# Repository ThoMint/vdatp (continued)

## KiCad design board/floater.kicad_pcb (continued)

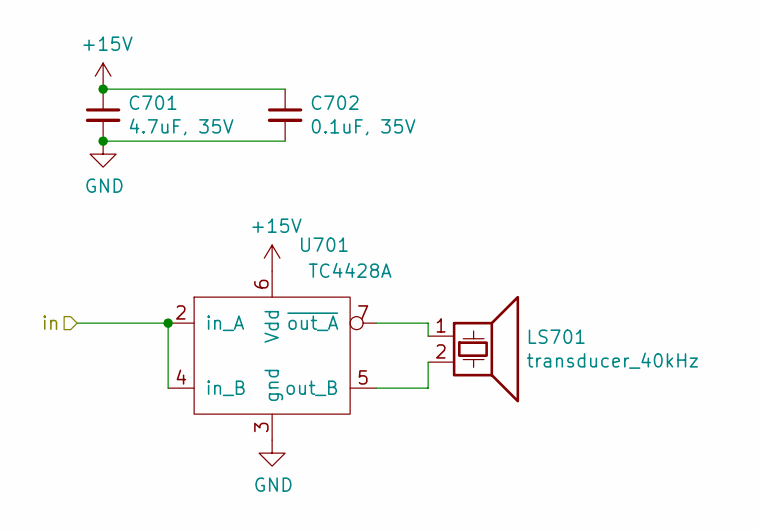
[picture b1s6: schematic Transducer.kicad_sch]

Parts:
C701: 4.7uF, 35V; C_1206_3216Metric
C702: 0.1uF, 35V; C_0805_2012Metric
LS701: transducer_40kHz; MSO-P1040H07T
U701: TC4428A; SO-8_3.9x4.9mm_P1.27mm

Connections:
+15V: C701.1, C702.1, U701.6 (Vdd); also elsewhere on the board
/FPGA2/t41: U701.2 (in_A), U701.4 (in_B); also elsewhere on the board
GND: C701.2, C702.2, U701.3 (gnd); also elsewhere on the board
unnamed: LS701.1, U701.7 (~out_A)
unnamed: LS701.2, U701.5 (out_B)

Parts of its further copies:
C601, C801, C901, C1001, C1101, C1201, C1301, C1401, C1501, C1601, C1701, C1801, C1901, C2001, C2101, C2201, C2301, C2401, C2501, C2601, C2701, C2801, C2901, C3001, C3101, C3201, C3301, C3401, C3501, C3601, C3701, C3801, C3901, C4001, C4101, C4201, C4301, C4401, C4501, C4601, C4701, C4801, C4901, C5001, C5101, C5201, C5301, C5401, C5501, C5601, C5701, C5801, C5901, C6001, C6101, C6201, C6301, C6401, C6501, C6601, C6701, C6801, C6901, C7001, C7101, C7201, C7301, C7401, C7501, C7601, C7701, C7801, C7901, C8001, C8101, C8201, C8301, C8401, C8501, C8601, C8701, C8801, C8901, C9001, C9101, C9201, C9301, C9401, C9501, C9601, C9701, C9801, C9901, C10001, C10101, C10201, C10301, C10401, C10501: 4.7uF, 35V; C_1206_3216Metric
C602, C802, C902, C1002, C1102, C1202, C1302, C1402, C1502, C1602, C1702, C1802, C1902, C2002, C2102, C2202, C2302, C2402, C2502, C2602, C2702, C2802, C2902, C3002, C3102, C3202, C3302, C3402, C3502, C3602, C3702, C3802, C3902, C4002, C4102, C4202, C4302, C4402, C4502, C4602, C4702, C4802, C4902, C5002, C5102, C5202, C5302, C5402, C5502, C5602, C5702, C5802, C5902, C6002, C6102, C6202, C6302, C6402, C6502, C6602, C6702, C6802, C6902, C7002, C7102, C7202, C7302, C7402, C7502, C7602, C7702, C7802, C7902, C8002, C8102, C8202, C8302, C8402, C8502, C8602, C8702, C8802, C8902, C9002, C9102, C9202, C9302, C9402, C9502, C9602, C9702, C9802, C9902, C10002, C10102, C10202, C10302, C10402, C10502: 0.1uF, 35V; C_0805_2012Metric
LS601, LS801, LS901, LS1001, LS1101, LS1201, LS1301, LS1401, LS1501, LS1601, LS1701, LS1801, LS1901, LS2001, LS2101, LS2201, LS2301, LS2401, LS2501, LS2601, LS2701, LS2801, LS2901, LS3001, LS3101, LS3201, LS3301, LS3401, LS3501, LS3601, LS3701, LS3801, LS3901, LS4001, LS4101, LS4201, LS4301, LS4401, LS4501, LS4601, LS4701, LS4801, LS4901, LS5001, LS5101, LS5201, LS5301, LS5401, LS5501, LS5601, LS5701, LS5801, LS5901, LS6001, LS6101, LS6201, LS6301, LS6401, LS6501, LS6601, LS6701, LS6801, LS6901, LS7001, LS7101, LS7201, LS7301, LS7401, LS7501, LS7601, LS7701, LS7801, LS7901, LS8001, LS8101, LS8201, LS8301, LS8401, LS8501, LS8601, LS8701, LS8801, LS8901, LS9001, LS9101, LS9201, LS9301, LS9401, LS9501, LS9601, LS9701, LS9801, LS9901, LS10001, LS10101, LS10201, LS10301, LS10401, LS10501: transducer_40kHz; MSO-P1040H07T
U601, U801, U901, U1001, U1101, U1201, U1301, U1401, U1501, U1601, U1701, U1801, U1901, U2001, U2101, U2201, U2301, U2401, U2501, U2601, U2701, U2801, U2901, U3001, U3101, U3201, U3301, U3401, U3501, U3601, U3701, U3801, U3901, U4001, U4101, U4201, U4301, U4401, U4501, U4601, U4701, U4801, U4901, U5001, U5101, U5201, U5301, U5401, U5501, U5601, U5701, U5801, U5901, U6001, U6101, U6201, U6301, U6401, U6501, U6601, U6701, U6801, U6901, U7001, U7101, U7201, U7301, U7401, U7501, U7601, U7701, U7801, U7901, U8001, U8101, U8201, U8301, U8401, U8501, U8601, U8701, U8801, U8901, U9001, U9101, U9201, U9301, U9401, U9501, U9601, U9701, U9801, U9901, U10001, U10101, U10201, U10301, U10401, U10501: TC4428A; SO-8_3.9x4.9mm_P1.27mm

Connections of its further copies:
+15V: C601.1, C602.1, C801.1, C802.1, C901.1, C902.1, C1001.1, C1002.1, C1101.1, C1102.1, C1201.1, C1202.1, C1301.1, C1302.1, C1401.1, C1402.1, C1501.1, C1502.1, C1601.1, C1602.1, C1701.1, C1702.1, C1801.1, C1802.1, C1901.1, C1902.1, C2001.1, C2002.1, C2101.1, C2102.1, C2201.1, C2202.1, C2301.1, C2302.1, C2401.1, C2402.1, C2501.1, C2502.1, C2601.1, C2602.1, C2701.1, C2702.1, C2801.1, C2802.1, C2901.1, C2902.1, C3001.1, C3002.1, C3101.1, C3102.1, C3201.1, C3202.1, C3301.1, C3302.1, C3401.1, C3402.1, C3501.1, C3502.1, C3601.1, C3602.1, C3701.1, C3702.1, C3801.1, C3802.1, C3901.1, C3902.1, C4001.1, C4002.1, C4101.1, C4102.1, C4201.1, C4202.1, C4301.1, C4302.1, C4401.1, C4402.1, C4501.1, C4502.1, C4601.1, C4602.1, C4701.1, C4702.1, C4801.1, C4802.1, C4901.1, C4902.1, C5001.1, C5002.1, C5101.1, C5102.1, C5201.1, C5202.1, C5301.1, C5302.1, C5401.1, C5402.1, C5501.1, C5502.1, C5601.1, C5602.1, C5701.1, C5702.1, C5801.1, C5802.1, C5901.1, C5902.1, C6001.1, C6002.1, C6101.1, C6102.1, C6201.1, C6202.1, C6301.1, C6302.1, C6401.1, C6402.1, C6501.1, C6502.1, C6601.1, C6602.1, C6701.1, C6702.1, C6801.1, C6802.1, C6901.1, C6902.1, C7001.1, C7002.1, C7101.1, C7102.1, C7201.1, C7202.1, C7301.1, C7302.1, C7401.1, C7402.1, C7501.1, C7502.1, C7601.1, C7602.1, C7701.1, C7702.1, C7801.1, C7802.1, C7901.1, C7902.1, C8001.1, C8002.1, C8101.1, C8102.1, C8201.1, C8202.1, C8301.1, C8302.1, C8401.1, C8402.1, C8501.1, C8502.1, C8601.1, C8602.1, C8701.1, C8702.1, C8801.1, C8802.1, C8901.1, C8902.1, C9001.1, C9002.1, C9101.1, C9102.1, C9201.1, C9202.1, C9301.1, C9302.1, C9401.1, C9402.1, C9501.1, C9502.1, C9601.1, C9602.1, C9701.1, C9702.1, C9801.1, C9802.1, C9901.1, C9902.1, C10001.1, C10002.1, C10101.1, C10102.1, C10201.1, C10202.1, C10301.1, C10302.1, C10401.1, C10402.1, C10501.1, C10502.1, U601.6 (Vdd), U801.6 (Vdd), U901.6 (Vdd), U1001.6 (Vdd), U1101.6 (Vdd), U1201.6 (Vdd), U1301.6 (Vdd), U1401.6 (Vdd), U1501.6 (Vdd), U1601.6 (Vdd), U1701.6 (Vdd), U1801.6 (Vdd), U1901.6 (Vdd), U2001.6 (Vdd), U2101.6 (Vdd), U2201.6 (Vdd), U2301.6 (Vdd), U2401.6 (Vdd), U2501.6 (Vdd), U2601.6 (Vdd), U2701.6 (Vdd), U2801.6 (Vdd), U2901.6 (Vdd), U3001.6 (Vdd), U3101.6 (Vdd), U3201.6 (Vdd), U3301.6 (Vdd), U3401.6 (Vdd), U3501.6 (Vdd), U3601.6 (Vdd), U3701.6 (Vdd), U3801.6 (Vdd), U3901.6 (Vdd), U4001.6 (Vdd), U4101.6 (Vdd), U4201.6 (Vdd), U4301.6 (Vdd), U4401.6 (Vdd), U4501.6 (Vdd), U4601.6 (Vdd), U4701.6 (Vdd), U4801.6 (Vdd), U4901.6 (Vdd), U5001.6 (Vdd), U5101.6 (Vdd), U5201.6 (Vdd), U5301.6 (Vdd), U5401.6 (Vdd), U5501.6 (Vdd), U5601.6 (Vdd), U5701.6 (Vdd), U5801.6 (Vdd), U5901.6 (Vdd), U6001.6 (Vdd), U6101.6 (Vdd), U6201.6 (Vdd), U6301.6 (Vdd), U6401.6 (Vdd), U6501.6 (Vdd), U6601.6 (Vdd), U6701.6 (Vdd), U6801.6 (Vdd), U6901.6 (Vdd), U7001.6 (Vdd), U7101.6 (Vdd), U7201.6 (Vdd), U7301.6 (Vdd), U7401.6 (Vdd), U7501.6 (Vdd), U7601.6 (Vdd), U7701.6 (Vdd), U7801.6 (Vdd), U7901.6 (Vdd), U8001.6 (Vdd), U8101.6 (Vdd), U8201.6 (Vdd), U8301.6 (Vdd), U8401.6 (Vdd), U8501.6 (Vdd), U8601.6 (Vdd), U8701.6 (Vdd), U8801.6 (Vdd), U8901.6 (Vdd), U9001.6 (Vdd), U9101.6 (Vdd), U9201.6 (Vdd), U9301.6 (Vdd), U9401.6 (Vdd), U9501.6 (Vdd), U9601.6 (Vdd), U9701.6 (Vdd), U9801.6 (Vdd), U9901.6 (Vdd), U10001.6 (Vdd), U10101.6 (Vdd), U10201.6 (Vdd), U10301.6 (Vdd), U10401.6 (Vdd), U10501.6 (Vdd); also elsewhere on the board
/FPGA2/t0: U4601.2 (in_A), U4601.4 (in_B); also elsewhere on the board
/FPGA2/t1: U4701.2 (in_A), U4701.4 (in_B); also elsewhere on the board
/FPGA2/t2: U4801.2 (in_A), U4801.4 (in_B); also elsewhere on the board
/FPGA2/t3: U4901.2 (in_A), U4901.4 (in_B); also elsewhere on the board
/FPGA2/t4: U5001.2 (in_A), U5001.4 (in_B); also elsewhere on the board
/FPGA2/t5: U5101.2 (in_A), U5101.4 (in_B); also elsewhere on the board
/FPGA2/t6: U5201.2 (in_A), U5201.4 (in_B); also elsewhere on the board
/FPGA2/t7: U5301.2 (in_A), U5301.4 (in_B); also elsewhere on the board
/FPGA2/t8: U5401.2 (in_A), U5401.4 (in_B); also elsewhere on the board
/FPGA2/t9: U5501.2 (in_A), U5501.4 (in_B); also elsewhere on the board
/FPGA2/t10: U3601.2 (in_A), U3601.4 (in_B); also elsewhere on the board
/FPGA2/t11: U3701.2 (in_A), U3701.4 (in_B); also elsewhere on the board
/FPGA2/t12: U3801.2 (in_A), U3801.4 (in_B); also elsewhere on the board
/FPGA2/t13: U3901.2 (in_A), U3901.4 (in_B); also elsewhere on the board
/FPGA2/t14: U4001.2 (in_A), U4001.4 (in_B); also elsewhere on the board
/FPGA2/t15: U4101.2 (in_A), U4101.4 (in_B); also elsewhere on the board
/FPGA2/t16: U4201.2 (in_A), U4201.4 (in_B); also elsewhere on the board
/FPGA2/t17: U4301.2 (in_A), U4301.4 (in_B); also elsewhere on the board
/FPGA2/t18: U4401.2 (in_A), U4401.4 (in_B); also elsewhere on the board
/FPGA2/t19: U4501.2 (in_A), U4501.4 (in_B); also elsewhere on the board
/FPGA2/t20: U2601.2 (in_A), U2601.4 (in_B); also elsewhere on the board
/FPGA2/t21: U2701.2 (in_A), U2701.4 (in_B); also elsewhere on the board
/FPGA2/t22: U2801.2 (in_A), U2801.4 (in_B); also elsewhere on the board
/FPGA2/t23: U2901.2 (in_A), U2901.4 (in_B); also elsewhere on the board
/FPGA2/t24: U3001.2 (in_A), U3001.4 (in_B); also elsewhere on the board
/FPGA2/t25: U3101.2 (in_A), U3101.4 (in_B); also elsewhere on the board
/FPGA2/t26: U3201.2 (in_A), U3201.4 (in_B); also elsewhere on the board
/FPGA2/t27: U3301.2 (in_A), U3301.4 (in_B); also elsewhere on the board
/FPGA2/t28: U3401.2 (in_A), U3401.4 (in_B); also elsewhere on the board
/FPGA2/t29: U3501.2 (in_A), U3501.4 (in_B); also elsewhere on the board
/FPGA2/t30: U1601.2 (in_A), U1601.4 (in_B); also elsewhere on the board
/FPGA2/t31: U1701.2 (in_A), U1701.4 (in_B); also elsewhere on the board
/FPGA2/t32: U1801.2 (in_A), U1801.4 (in_B); also elsewhere on the board
/FPGA2/t33: U1901.2 (in_A), U1901.4 (in_B); also elsewhere on the board
/FPGA2/t34: U2001.2 (in_A), U2001.4 (in_B); also elsewhere on the board
/FPGA2/t35: U2101.2 (in_A), U2101.4 (in_B); also elsewhere on the board
/FPGA2/t36: U2201.2 (in_A), U2201.4 (in_B); also elsewhere on the board
/FPGA2/t37: U2301.2 (in_A), U2301.4 (in_B); also elsewhere on the board
/FPGA2/t38: U2401.2 (in_A), U2401.4 (in_B); also elsewhere on the board
/FPGA2/t39: U2501.2 (in_A), U2501.4 (in_B); also elsewhere on the board
/FPGA2/t40: U601.2 (in_A), U601.4 (in_B); also elsewhere on the board
/FPGA2/t42: U801.2 (in_A), U801.4 (in_B); also elsewhere on the board
/FPGA2/t43: U901.2 (in_A), U901.4 (in_B); also elsewhere on the board
/FPGA2/t44: U1001.2 (in_A), U1001.4 (in_B); also elsewhere on the board
/FPGA2/t45: U1101.2 (in_A), U1101.4 (in_B); also elsewhere on the board
/FPGA2/t46: U1201.2 (in_A), U1201.4 (in_B); also elsewhere on the board
/FPGA2/t47: U1301.2 (in_A), U1301.4 (in_B); also elsewhere on the board
/FPGA2/t48: U1401.2 (in_A), U1401.4 (in_B); also elsewhere on the board
/FPGA2/t49: U1501.2 (in_A), U1501.4 (in_B); also elsewhere on the board
/Transducers/s0: U9601.2 (in_A), U9601.4 (in_B); also elsewhere on the board
/Transducers/s1: U9701.2 (in_A), U9701.4 (in_B); also elsewhere on the board
/Transducers/s2: U9801.2 (in_A), U9801.4 (in_B); also elsewhere on the board
/Transducers/s3: U9901.2 (in_A), U9901.4 (in_B); also elsewhere on the board
/Transducers/s4: U10001.2 (in_A), U10001.4 (in_B); also elsewhere on the board
/Transducers/s5: U10101.2 (in_A), U10101.4 (in_B); also elsewhere on the board
/Transducers/s6: U10201.2 (in_A), U10201.4 (in_B); also elsewhere on the board
/Transducers/s7: U10301.2 (in_A), U10301.4 (in_B); also elsewhere on the board
/Transducers/s8: U10401.2 (in_A), U10401.4 (in_B); also elsewhere on the board
/Transducers/s9: U10501.2 (in_A), U10501.4 (in_B); also elsewhere on the board
/Transducers/s10: U8601.2 (in_A), U8601.4 (in_B); also elsewhere on the board
/Transducers/s11: U8701.2 (in_A), U8701.4 (in_B); also elsewhere on the board
/Transducers/s12: U8801.2 (in_A), U8801.4 (in_B); also elsewhere on the board
/Transducers/s13: U8901.2 (in_A), U8901.4 (in_B); also elsewhere on the board
/Transducers/s14: U9001.2 (in_A), U9001.4 (in_B); also elsewhere on the board
/Transducers/s15: U9101.2 (in_A), U9101.4 (in_B); also elsewhere on the board
/Transducers/s16: U9201.2 (in_A), U9201.4 (in_B); also elsewhere on the board
/Transducers/s17: U9301.2 (in_A), U9301.4 (in_B); also elsewhere on the board
/Transducers/s18: U9401.2 (in_A), U9401.4 (in_B); also elsewhere on the board
/Transducers/s19: U9501.2 (in_A), U9501.4 (in_B); also elsewhere on the board
/Transducers/s20: U7601.2 (in_A), U7601.4 (in_B); also elsewhere on the board
/Transducers/s21: U7701.2 (in_A), U7701.4 (in_B); also elsewhere on the board
/Transducers/s22: U7801.2 (in_A), U7801.4 (in_B); also elsewhere on the board
/Transducers/s23: U7901.2 (in_A), U7901.4 (in_B); also elsewhere on the board
/Transducers/s24: U8001.2 (in_A), U8001.4 (in_B); also elsewhere on the board
/Transducers/s25: U8101.2 (in_A), U8101.4 (in_B); also elsewhere on the board
/Transducers/s26: U8201.2 (in_A), U8201.4 (in_B); also elsewhere on the board
/Transducers/s27: U8301.2 (in_A), U8301.4 (in_B); also elsewhere on the board
/Transducers/s28: U8401.2 (in_A), U8401.4 (in_B); also elsewhere on the board
/Transducers/s29: U8501.2 (in_A), U8501.4 (in_B); also elsewhere on the board
/Transducers/s30: U6601.2 (in_A), U6601.4 (in_B); also elsewhere on the board
/Transducers/s31: U6701.2 (in_A), U6701.4 (in_B); also elsewhere on the board
/Transducers/s32: U6801.2 (in_A), U6801.4 (in_B); also elsewhere on the board
/Transducers/s33: U6901.2 (in_A), U6901.4 (in_B); also elsewhere on the board
/Transducers/s34: U7001.2 (in_A), U7001.4 (in_B); also elsewhere on the board
/Transducers/s35: U7101.2 (in_A), U7101.4 (in_B); also elsewhere on the board
/Transducers/s36: U7201.2 (in_A), U7201.4 (in_B); also elsewhere on the board
/Transducers/s37: U7301.2 (in_A), U7301.4 (in_B); also elsewhere on the board
/Transducers/s38: U7401.2 (in_A), U7401.4 (in_B); also elsewhere on the board
/Transducers/s39: U7501.2 (in_A), U7501.4 (in_B); also elsewhere on the board
/Transducers/s40: U5601.2 (in_A), U5601.4 (in_B); also elsewhere on the board
/Transducers/s41: U5701.2 (in_A), U5701.4 (in_B); also elsewhere on the board
/Transducers/s42: U5801.2 (in_A), U5801.4 (in_B); also elsewhere on the board
/Transducers/s43: U5901.2 (in_A), U5901.4 (in_B); also elsewhere on the board
/Transducers/s44: U6001.2 (in_A), U6001.4 (in_B); also elsewhere on the board
/Transducers/s45: U6101.2 (in_A), U6101.4 (in_B); also elsewhere on the board
/Transducers/s46: U6201.2 (in_A), U6201.4 (in_B); also elsewhere on the board
/Transducers/s47: U6301.2 (in_A), U6301.4 (in_B); also elsewhere on the board
/Transducers/s48: U6401.2 (in_A), U6401.4 (in_B); also elsewhere on the board
/Transducers/s49: U6501.2 (in_A), U6501.4 (in_B); also elsewhere on the board
GND: C601.2, C602.2, C801.2, C802.2, C901.2, C902.2, C1001.2, C1002.2, C1101.2, C1102.2, C1201.2, C1202.2, C1301.2, C1302.2, C1401.2, C1402.2, C1501.2, C1502.2, C1601.2, C1602.2, C1701.2, C1702.2, C1801.2, C1802.2, C1901.2, C1902.2, C2001.2, C2002.2, C2101.2, C2102.2, C2201.2, C2202.2, C2301.2, C2302.2, C2401.2, C2402.2, C2501.2, C2502.2, C2601.2, C2602.2, C2701.2, C2702.2, C2801.2, C2802.2, C2901.2, C2902.2, C3001.2, C3002.2, C3101.2, C3102.2, C3201.2, C3202.2, C3301.2, C3302.2, C3401.2, C3402.2, C3501.2, C3502.2, C3601.2, C3602.2, C3701.2, C3702.2, C3801.2, C3802.2, C3901.2, C3902.2, C4001.2, C4002.2, C4101.2, C4102.2, C4201.2, C4202.2, C4301.2, C4302.2, C4401.2, C4402.2, C4501.2, C4502.2, C4601.2, C4602.2, C4701.2, C4702.2, C4801.2, C4802.2, C4901.2, C4902.2, C5001.2, C5002.2, C5101.2, C5102.2, C5201.2, C5202.2, C5301.2, C5302.2, C5401.2, C5402.2, C5501.2, C5502.2, C5601.2, C5602.2, C5701.2, C5702.2, C5801.2, C5802.2, C5901.2, C5902.2, C6001.2, C6002.2, C6101.2, C6102.2, C6201.2, C6202.2, C6301.2, C6302.2, C6401.2, C6402.2, C6501.2, C6502.2, C6601.2, C6602.2, C6701.2, C6702.2, C6801.2, C6802.2, C6901.2, C6902.2, C7001.2, C7002.2, C7101.2, C7102.2, C7201.2, C7202.2, C7301.2, C7302.2, C7401.2, C7402.2, C7501.2, C7502.2, C7601.2, C7602.2, C7701.2, C7702.2, C7801.2, C7802.2, C7901.2, C7902.2, C8001.2, C8002.2, C8101.2, C8102.2, C8201.2, C8202.2, C8301.2, C8302.2, C8401.2, C8402.2, C8501.2, C8502.2, C8601.2, C8602.2, C8701.2, C8702.2, C8801.2, C8802.2, C8901.2, C8902.2, C9001.2, C9002.2, C9101.2, C9102.2, C9201.2, C9202.2, C9301.2, C9302.2, C9401.2, C9402.2, C9501.2, C9502.2, C9601.2, C9602.2, C9701.2, C9702.2, C9801.2, C9802.2, C9901.2, C9902.2, C10001.2, C10002.2, C10101.2, C10102.2, C10201.2, C10202.2, C10301.2, C10302.2, C10401.2, C10402.2, C10501.2, C10502.2, U601.3 (gnd), U801.3 (gnd), U901.3 (gnd), U1001.3 (gnd), U1101.3 (gnd), U1201.3 (gnd), U1301.3 (gnd), U1401.3 (gnd), U1501.3 (gnd), U1601.3 (gnd), U1701.3 (gnd), U1801.3 (gnd), U1901.3 (gnd), U2001.3 (gnd), U2101.3 (gnd), U2201.3 (gnd), U2301.3 (gnd), U2401.3 (gnd), U2501.3 (gnd), U2601.3 (gnd), U2701.3 (gnd), U2801.3 (gnd), U2901.3 (gnd), U3001.3 (gnd), U3101.3 (gnd), U3201.3 (gnd), U3301.3 (gnd), U3401.3 (gnd), U3501.3 (gnd), U3601.3 (gnd), U3701.3 (gnd), U3801.3 (gnd), U3901.3 (gnd), U4001.3 (gnd), U4101.3 (gnd), U4201.3 (gnd), U4301.3 (gnd), U4401.3 (gnd), U4501.3 (gnd), U4601.3 (gnd), U4701.3 (gnd), U4801.3 (gnd), U4901.3 (gnd), U5001.3 (gnd), U5101.3 (gnd), U5201.3 (gnd), U5301.3 (gnd), U5401.3 (gnd), U5501.3 (gnd), U5601.3 (gnd), U5701.3 (gnd), U5801.3 (gnd), U5901.3 (gnd), U6001.3 (gnd), U6101.3 (gnd), U6201.3 (gnd), U6301.3 (gnd), U6401.3 (gnd), U6501.3 (gnd), U6601.3 (gnd), U6701.3 (gnd), U6801.3 (gnd), U6901.3 (gnd), U7001.3 (gnd), U7101.3 (gnd), U7201.3 (gnd), U7301.3 (gnd), U7401.3 (gnd), U7501.3 (gnd), U7601.3 (gnd), U7701.3 (gnd), U7801.3 (gnd), U7901.3 (gnd), U8001.3 (gnd), U8101.3 (gnd), U8201.3 (gnd), U8301.3 (gnd), U8401.3 (gnd), U8501.3 (gnd), U8601.3 (gnd), U8701.3 (gnd), U8801.3 (gnd), U8901.3 (gnd), U9001.3 (gnd), U9101.3 (gnd), U9201.3 (gnd), U9301.3 (gnd), U9401.3 (gnd), U9501.3 (gnd), U9601.3 (gnd), U9701.3 (gnd), U9801.3 (gnd), U9901.3 (gnd), U10001.3 (gnd), U10101.3 (gnd), U10201.3 (gnd), U10301.3 (gnd), U10401.3 (gnd), U10501.3 (gnd); also elsewhere on the board
unnamed: LS601.1, U601.7 (~out_A)
unnamed: LS601.2, U601.5 (out_B)
unnamed: LS801.1, U801.7 (~out_A)
unnamed: LS801.2, U801.5 (out_B)
unnamed: LS901.1, U901.7 (~out_A)
unnamed: LS901.2, U901.5 (out_B)
unnamed: LS1001.1, U1001.7 (~out_A)
unnamed: LS1001.2, U1001.5 (out_B)
unnamed: LS1101.1, U1101.7 (~out_A)
unnamed: LS1101.2, U1101.5 (out_B)
unnamed: LS1201.1, U1201.7 (~out_A)
unnamed: LS1201.2, U1201.5 (out_B)
unnamed: LS1301.1, U1301.7 (~out_A)
unnamed: LS1301.2, U1301.5 (out_B)
unnamed: LS1401.1, U1401.7 (~out_A)
unnamed: LS1401.2, U1401.5 (out_B)
unnamed: LS1501.1, U1501.7 (~out_A)
unnamed: LS1501.2, U1501.5 (out_B)
unnamed: LS1601.1, U1601.7 (~out_A)
unnamed: LS1601.2, U1601.5 (out_B)
unnamed: LS1701.1, U1701.7 (~out_A)
unnamed: LS1701.2, U1701.5 (out_B)
unnamed: LS1801.1, U1801.7 (~out_A)
unnamed: LS1801.2, U1801.5 (out_B)
unnamed: LS1901.1, U1901.7 (~out_A)
unnamed: LS1901.2, U1901.5 (out_B)
unnamed: LS2001.1, U2001.7 (~out_A)
unnamed: LS2001.2, U2001.5 (out_B)
unnamed: LS2101.1, U2101.7 (~out_A)
unnamed: LS2101.2, U2101.5 (out_B)
unnamed: LS2201.1, U2201.7 (~out_A)
unnamed: LS2201.2, U2201.5 (out_B)
unnamed: LS2301.1, U2301.7 (~out_A)
unnamed: LS2301.2, U2301.5 (out_B)
unnamed: LS2401.1, U2401.7 (~out_A)
unnamed: LS2401.2, U2401.5 (out_B)
unnamed: LS2501.1, U2501.7 (~out_A)
unnamed: LS2501.2, U2501.5 (out_B)
unnamed: LS2601.1, U2601.7 (~out_A)
unnamed: LS2601.2, U2601.5 (out_B)
unnamed: LS2701.1, U2701.7 (~out_A)
unnamed: LS2701.2, U2701.5 (out_B)
unnamed: LS2801.1, U2801.7 (~out_A)
unnamed: LS2801.2, U2801.5 (out_B)
unnamed: LS2901.1, U2901.7 (~out_A)
unnamed: LS2901.2, U2901.5 (out_B)
unnamed: LS3001.1, U3001.7 (~out_A)
unnamed: LS3001.2, U3001.5 (out_B)
unnamed: LS3101.1, U3101.7 (~out_A)
unnamed: LS3101.2, U3101.5 (out_B)
unnamed: LS3201.1, U3201.7 (~out_A)
unnamed: LS3201.2, U3201.5 (out_B)
unnamed: LS3301.1, U3301.7 (~out_A)
unnamed: LS3301.2, U3301.5 (out_B)
unnamed: LS3401.1, U3401.7 (~out_A)
unnamed: LS3401.2, U3401.5 (out_B)
unnamed: LS3501.1, U3501.7 (~out_A)
unnamed: LS3501.2, U3501.5 (out_B)
unnamed: LS3601.1, U3601.7 (~out_A)
unnamed: LS3601.2, U3601.5 (out_B)
unnamed: LS3701.1, U3701.7 (~out_A)
unnamed: LS3701.2, U3701.5 (out_B)
unnamed: LS3801.1, U3801.7 (~out_A)
unnamed: LS3801.2, U3801.5 (out_B)
unnamed: LS3901.1, U3901.7 (~out_A)
unnamed: LS3901.2, U3901.5 (out_B)
unnamed: LS4001.1, U4001.7 (~out_A)
unnamed: LS4001.2, U4001.5 (out_B)
unnamed: LS4101.1, U4101.7 (~out_A)
unnamed: LS4101.2, U4101.5 (out_B)
unnamed: LS4201.1, U4201.7 (~out_A)
unnamed: LS4201.2, U4201.5 (out_B)
unnamed: LS4301.1, U4301.7 (~out_A)
unnamed: LS4301.2, U4301.5 (out_B)
unnamed: LS4401.1, U4401.7 (~out_A)
unnamed: LS4401.2, U4401.5 (out_B)
unnamed: LS4501.1, U4501.7 (~out_A)
unnamed: LS4501.2, U4501.5 (out_B)
unnamed: LS4601.1, U4601.7 (~out_A)
unnamed: LS4601.2, U4601.5 (out_B)
unnamed: LS4701.1, U4701.7 (~out_A)
unnamed: LS4701.2, U4701.5 (out_B)
unnamed: LS4801.1, U4801.7 (~out_A)
unnamed: LS4801.2, U4801.5 (out_B)
unnamed: LS4901.1, U4901.7 (~out_A)
unnamed: LS4901.2, U4901.5 (out_B)
unnamed: LS5001.1, U5001.7 (~out_A)
unnamed: LS5001.2, U5001.5 (out_B)
unnamed: LS5101.1, U5101.7 (~out_A)
unnamed: LS5101.2, U5101.5 (out_B)
unnamed: LS5201.1, U5201.7 (~out_A)
unnamed: LS5201.2, U5201.5 (out_B)
unnamed: LS5301.1, U5301.7 (~out_A)
unnamed: LS5301.2, U5301.5 (out_B)
unnamed: LS5401.1, U5401.7 (~out_A)
unnamed: LS5401.2, U5401.5 (out_B)
unnamed: LS5501.1, U5501.7 (~out_A)
unnamed: LS5501.2, U5501.5 (out_B)
unnamed: LS5601.1, U5601.7 (~out_A)
unnamed: LS5601.2, U5601.5 (out_B)
unnamed: LS5701.1, U5701.7 (~out_A)
unnamed: LS5701.2, U5701.5 (out_B)
unnamed: LS5801.1, U5801.7 (~out_A)
unnamed: LS5801.2, U5801.5 (out_B)
unnamed: LS5901.1, U5901.7 (~out_A)
unnamed: LS5901.2, U5901.5 (out_B)
unnamed: LS6001.1, U6001.7 (~out_A)
unnamed: LS6001.2, U6001.5 (out_B)
unnamed: LS6101.1, U6101.7 (~out_A)
unnamed: LS6101.2, U6101.5 (out_B)
unnamed: LS6201.1, U6201.7 (~out_A)
unnamed: LS6201.2, U6201.5 (out_B)
unnamed: LS6301.1, U6301.7 (~out_A)
unnamed: LS6301.2, U6301.5 (out_B)
unnamed: LS6401.1, U6401.7 (~out_A)
unnamed: LS6401.2, U6401.5 (out_B)
unnamed: LS6501.1, U6501.7 (~out_A)
unnamed: LS6501.2, U6501.5 (out_B)
unnamed: LS6601.1, U6601.7 (~out_A)
unnamed: LS6601.2, U6601.5 (out_B)
unnamed: LS6701.1, U6701.7 (~out_A)
unnamed: LS6701.2, U6701.5 (out_B)
unnamed: LS6801.1, U6801.7 (~out_A)
unnamed: LS6801.2, U6801.5 (out_B)
unnamed: LS6901.1, U6901.7 (~out_A)
unnamed: LS6901.2, U6901.5 (out_B)
unnamed: LS7001.1, U7001.7 (~out_A)
unnamed: LS7001.2, U7001.5 (out_B)
unnamed: LS7101.1, U7101.7 (~out_A)
unnamed: LS7101.2, U7101.5 (out_B)
unnamed: LS7201.1, U7201.7 (~out_A)
unnamed: LS7201.2, U7201.5 (out_B)
unnamed: LS7301.1, U7301.7 (~out_A)
unnamed: LS7301.2, U7301.5 (out_B)
unnamed: LS7401.1, U7401.7 (~out_A)
unnamed: LS7401.2, U7401.5 (out_B)
unnamed: LS7501.1, U7501.7 (~out_A)
unnamed: LS7501.2, U7501.5 (out_B)
unnamed: LS7601.1, U7601.7 (~out_A)
unnamed: LS7601.2, U7601.5 (out_B)
unnamed: LS7701.1, U7701.7 (~out_A)
unnamed: LS7701.2, U7701.5 (out_B)
unnamed: LS7801.1, U7801.7 (~out_A)
unnamed: LS7801.2, U7801.5 (out_B)
unnamed: LS7901.1, U7901.7 (~out_A)
unnamed: LS7901.2, U7901.5 (out_B)
unnamed: LS8001.1, U8001.7 (~out_A)
unnamed: LS8001.2, U8001.5 (out_B)
unnamed: LS8101.1, U8101.7 (~out_A)
unnamed: LS8101.2, U8101.5 (out_B)
unnamed: LS8201.1, U8201.7 (~out_A)
unnamed: LS8201.2, U8201.5 (out_B)
unnamed: LS8301.1, U8301.7 (~out_A)
unnamed: LS8301.2, U8301.5 (out_B)
unnamed: LS8401.1, U8401.7 (~out_A)
unnamed: LS8401.2, U8401.5 (out_B)
unnamed: LS8501.1, U8501.7 (~out_A)
unnamed: LS8501.2, U8501.5 (out_B)
unnamed: LS8601.1, U8601.7 (~out_A)
unnamed: LS8601.2, U8601.5 (out_B)
unnamed: LS8701.1, U8701.7 (~out_A)
unnamed: LS8701.2, U8701.5 (out_B)
unnamed: LS8801.1, U8801.7 (~out_A)
unnamed: LS8801.2, U8801.5 (out_B)
unnamed: LS8901.1, U8901.7 (~out_A)
unnamed: LS8901.2, U8901.5 (out_B)
unnamed: LS9001.1, U9001.7 (~out_A)
unnamed: LS9001.2, U9001.5 (out_B)
unnamed: LS9101.1, U9101.7 (~out_A)
unnamed: LS9101.2, U9101.5 (out_B)
unnamed: LS9201.1, U9201.7 (~out_A)
unnamed: LS9201.2, U9201.5 (out_B)
unnamed: LS9301.1, U9301.7 (~out_A)
unnamed: LS9301.2, U9301.5 (out_B)
unnamed: LS9401.1, U9401.7 (~out_A)
unnamed: LS9401.2, U9401.5 (out_B)
unnamed: LS9501.1, U9501.7 (~out_A)
unnamed: LS9501.2, U9501.5 (out_B)
unnamed: LS9601.1, U9601.7 (~out_A)
unnamed: LS9601.2, U9601.5 (out_B)
unnamed: LS9701.1, U9701.7 (~out_A)
unnamed: LS9701.2, U9701.5 (out_B)
unnamed: LS9801.1, U9801.7 (~out_A)
unnamed: LS9801.2, U9801.5 (out_B)
unnamed: LS9901.1, U9901.7 (~out_A)
unnamed: LS9901.2, U9901.5 (out_B)
unnamed: LS10001.1, U10001.7 (~out_A)
unnamed: LS10001.2, U10001.5 (out_B)
unnamed: LS10101.1, U10101.7 (~out_A)
unnamed: LS10101.2, U10101.5 (out_B)
unnamed: LS10201.1, U10201.7 (~out_A)
unnamed: LS10201.2, U10201.5 (out_B)
unnamed: LS10301.1, U10301.7 (~out_A)
unnamed: LS10301.2, U10301.5 (out_B)
unnamed: LS10401.1, U10401.7 (~out_A)
unnamed: LS10401.2, U10401.5 (out_B)
unnamed: LS10501.1, U10501.7 (~out_A)
unnamed: LS10501.2, U10501.5 (out_B)

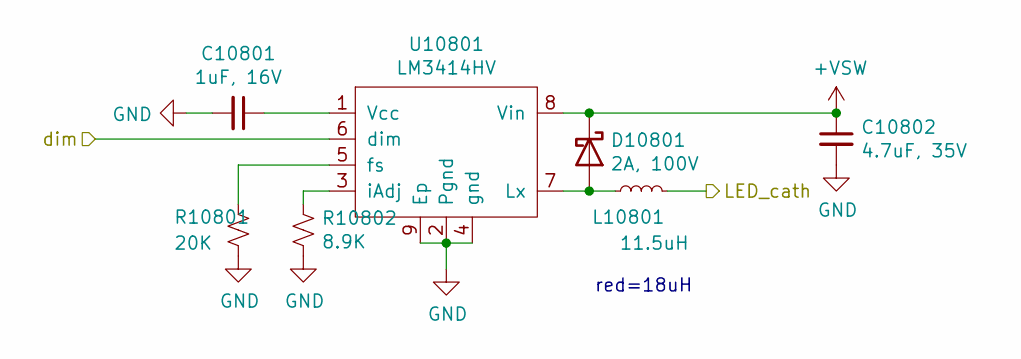
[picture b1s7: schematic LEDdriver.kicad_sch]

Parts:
C10801: 1uF, 16V; C_0805_2012Metric
C10802: 4.7uF, 35V; C_1206_3216Metric
D10801: 2A, 100V; DO-220A
L10801: 11.5uH; SRR6038
R10801: 20K; R_0402_1005Metric
R10802: 8.9K; R_0402_1005Metric
U10801: LM3414HV; SOIC-8-1EP_3.9x4.9mm_P1.27mm_EP2.35x2.35mm

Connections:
+VSW: C10802.1, D10801.1 (K), U10801.8 (Vin); also elsewhere on the board
/LED/sheet5F55454A/LED_cath: L10801.2; also elsewhere on the board
/greenDim: U10801.6 (dim); also elsewhere on the board
GND: C10801.2, C10802.2, R10801.1, R10802.2, U10801.2 (Pgnd), U10801.4 (gnd), U10801.9 (Ep); also elsewhere on the board
unnamed: C10801.1, U10801.1 (Vcc)
unnamed: D10801.2 (A), L10801.1, U10801.7 (Lx)
unnamed: R10801.2, U10801.5 (fs)
unnamed: R10802.1, U10801.3 (iAdj)

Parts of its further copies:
C10701, C10901: 1uF, 16V; C_0805_2012Metric
C10702, C10902: 4.7uF, 35V; C_1206_3216Metric
D10701, D10901: 2A, 100V; DO-220A
L10701, L10901: 11.5uH; SRR6038
R10701, R10901: 20K; R_0402_1005Metric
R10702, R10902: 8.9K; R_0402_1005Metric
U10701, U10901: LM3414HV; SOIC-8-1EP_3.9x4.9mm_P1.27mm_EP2.35x2.35mm

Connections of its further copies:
+VSW: C10702.1, C10902.1, D10701.1 (K), D10901.1 (K), U10701.8 (Vin), U10901.8 (Vin); also elsewhere on the board
/LED/LED driver/LED_cath: L10701.2; also elsewhere on the board
/LED/sheet5F55462D/LED_cath: L10901.2; also elsewhere on the board
/blueDim: U10901.6 (dim); also elsewhere on the board
/redDim: U10701.6 (dim); also elsewhere on the board
GND: C10701.2, C10702.2, C10901.2, C10902.2, R10701.1, R10702.2, R10901.1, R10902.2, U10701.2 (Pgnd), U10701.4 (gnd), U10701.9 (Ep), U10901.2 (Pgnd), U10901.4 (gnd), U10901.9 (Ep); also elsewhere on the board
unnamed: C10701.1, U10701.1 (Vcc)
unnamed: C10901.1, U10901.1 (Vcc)
unnamed: D10701.2 (A), L10701.1, U10701.7 (Lx)
unnamed: D10901.2 (A), L10901.1, U10901.7 (Lx)
unnamed: R10701.2, U10701.5 (fs)
unnamed: R10702.1, U10701.3 (iAdj)
unnamed: R10901.2, U10901.5 (fs)
unnamed: R10902.1, U10901.3 (iAdj)

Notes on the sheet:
red=18uH

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
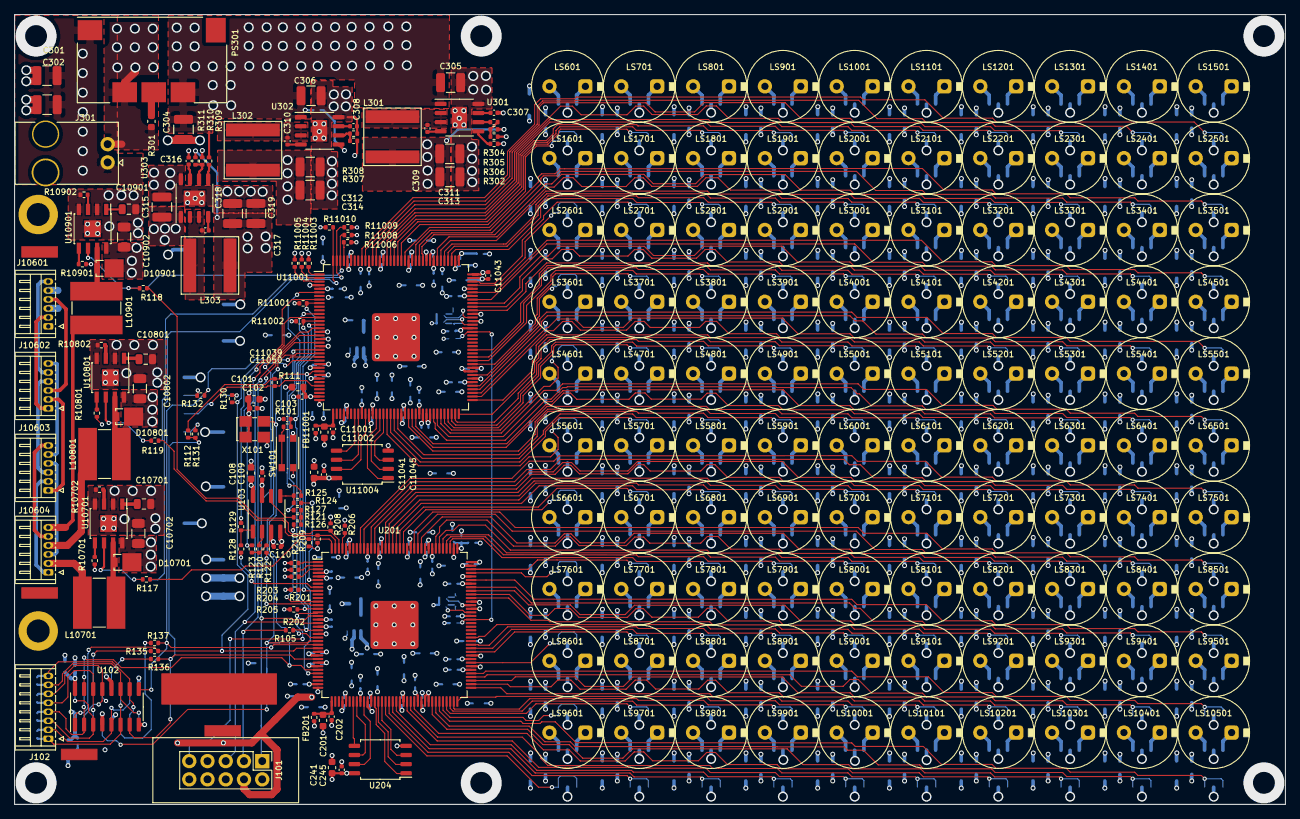
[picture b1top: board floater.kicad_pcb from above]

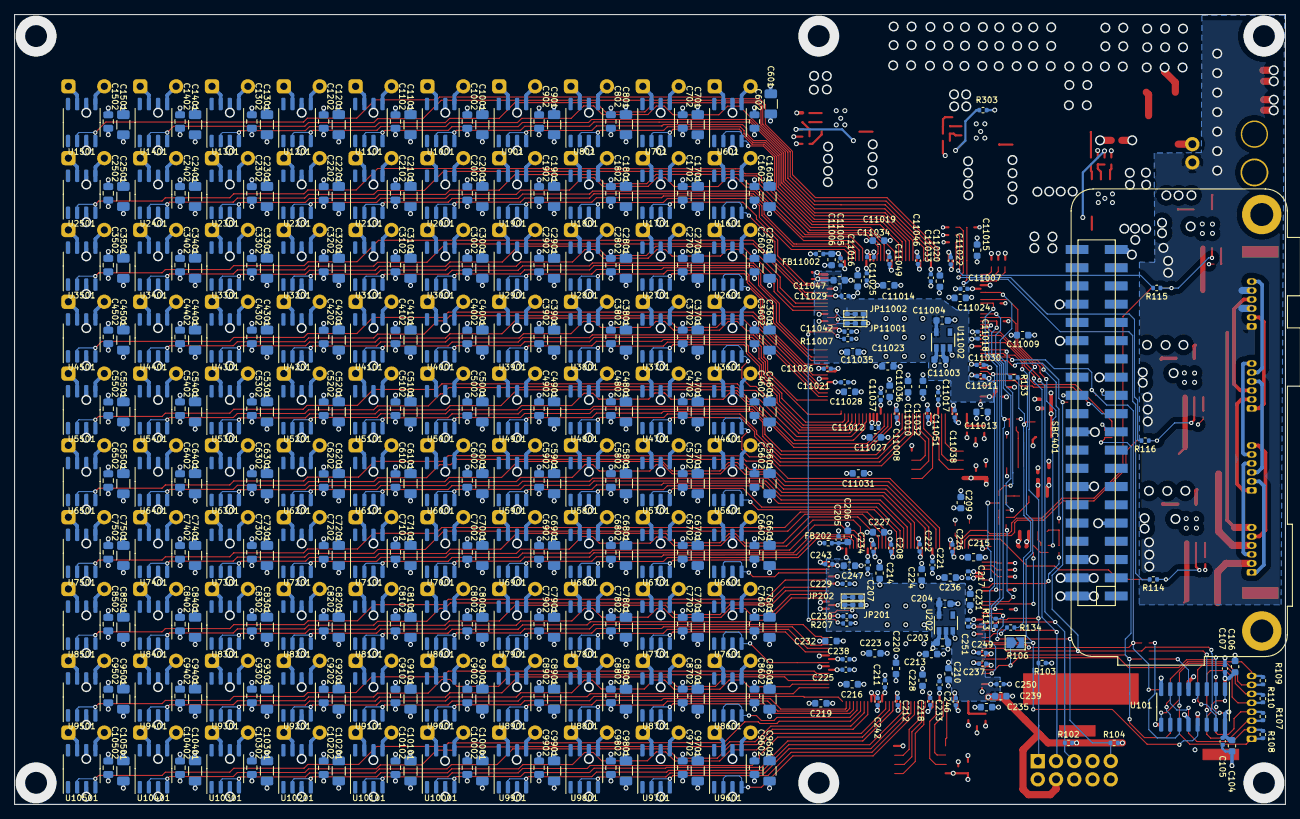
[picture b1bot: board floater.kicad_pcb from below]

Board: 4 copper layers, 177.0 x 110.0 mm, 647 parts (416 on the bottom side), 433 nets.

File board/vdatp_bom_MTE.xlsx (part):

|  |  |  | per PCB | Gesamtbestellmenge | Hersteller | Teilenummer | Link | Preis | Preis für 2 Stk | Info
> C101, C104, C106, C201, C203, C204, C206, C209, C210, C213-C216, C219, C220, 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 | 4.7uF | Capacitor_SMD:C_0603_1608Metric |  | 51 | 102 | Samsung | CL10A475KP8NNNC | MTE-ID 5653, Stock 3215 | 0 | 0 | 6.3V type
> C102, C103, C105, C107, C202, C205, C207, C208, C211, C212, C217, C218, C221,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 | 0.1uF | Capacitor_SMD:C_0402_1005Metric |  | 64 | 128 |  |  | MTE-ID 6867, Stock 3711 | 0 | 0 | 50V type
> C301, C302 | 10uF,50V | Resistor_SMD:R_1210_3225Metric |  | 2 | 4 |  |  | MTE-ID 6670, Stock 100 | 0 | 0
> C304-C306, C315 | 22uF,35V | Capacitor_SMD:C_1210_3225Metric |  | 10 | 20 |  |  | MTE-ID 5803, Stock 34 | 0 | 0 | downrated to 25V
> C311-C314, C318, C319 | 22uF | Capacitor_SMD:C_1210_3225Metric |  | 6 | 12 |  |  | MTE-ID 2613, Stock 315 | 0 | 0 | downrated to 6V
> C601, C701, C801, C901, C1001, C1101, C1201, C1301, C1401, C1501, C1601, C170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 | 4.7uF, 35V | Capacitor_SMD:C_1206_3216Metric | 1276-2880-2-ND | 103 | 206 | Samsung Electro Mechanics | CL31A475KAHNNNE | https://www.digikey.at/product-detail/de/samsung-electro-mec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 | 7.9000000000000001E-2 | 16.274000000000001 | downrated to 25V
> C602, C702, C802, C902, C1002, C1102, C1202, C1302, C1402, C1502, C1602, C170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 | 0.1uF, 35V | Capacitor_SMD:C_0805_2012Metric |  | 100 | 200 |  |  | MTE-ID 1118, Stock 1273 | 0 | 0
> C10701, C10801, C10901 | 1uF, 16V | Capacitor_SMD:C_0805_2012Metric |  | 3 | 6 |  |  | MTE-ID 2896, Stock 1000 | 0 | 0
> D10701, D10801, D10901 | 2A, 100V | holo:DO-220A | SS2PH10-M3/84AGICT-ND | 3 | 6 | Vishay | SS2PH10-M3/84A | https://at.farnell.com/vishay/ss2ph10-m3-84a/gleichr-diode-s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 | 0.24 | 1.44
> FB201, FB202, FB11001, FB11002 | 300R | Resistor_SMD:R_0402_1005Metric | 535-12548-1-ND | 4 | 8 | Abracon | ACML-0402HC-301-T | https://www.digikey.at/products/de?keywords=535-12548-1-ND | 5.3999999999999999E-2 | 0.432
J101 | JTAG | Connector_PinHeader_2.54mm:PinHeader_2x05_P2.54mm_Vertical_Shrouded | 732-2094-ND | 1 | 2 | Würth | 61201021621 | https://www.digikey.at/products/de?keywords=732-2094-ND | 0.38 | 0.76
J102 | Comms | Connector_Hirose:Hirose_DF13-08P-1.25DS_1x08_P1.25mm_Horizontal | H2205-ND | 1 | 2 | Hirose | DF13-8P-1.25DS(20) | https://www.digikey.at/products/de?keywords=H2205-ND | 0.68 | 1.36 | kann das sein, dass das einfach JST sind?
J301 | Power | Connector_Molex:Molex_70555_RA_1x02_P2.54 | WM14786 | 1 | 2 | Molex | 705550071 | https://www.digikey.at/products/de?keywords=WM14786 | 0.89 | 1.78
> J10601-J10604 | Screw_Terminal_01x06 | Connector_Hirose:Hirose_DF13-06P-1.25DS_1x06_P1.25mm_Horizontal | H2203-ND | 4 | 8 | Hirose | DF13-6P-1.25DS(20) | https://www.digikey.at/product-detail/de/hirose-electric-co-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 | 0.54200000000000004 | 4.3360000000000003
L301 | 2.0uH | holo:NR8040 | 587-1997-1-ND | 1 | 2 | Tayo Yuden | NRS8040T2R0NJGJ | https://www.digikey.at/product-detail/de/NRS8040T2R0NJGJ/587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 | 0.38 | 0.76 | Alternativtyp
L302 | 3.6uH | holo:NR8040 | 587-1998-1-ND | 1 | 2 | Tayo Yuden | NR8040T3R6N | https://www.digikey.at/products/de?keywords=587-1998-1-ND | 0.46 | 0.92
L303 | 4.7uH | holo:NR8040 | 587-1999-1-ND | 1 | 2 | Tayo Yuden | NR8040T4R7N | https://www.digikey.at/products/de?keywords=587-1999-1-ND | 0.46 | 0.92
> L10701, L10801 | 11.5uH | holo:SRR6038 | SRR6038-120YCT-ND | 2 | 4 | Bourns | SRR6038-120Y | https://www.digikey.at/products/de?keywords=SRR6038-120YCT-ND | 0.72 | 2.88
L10901 | 18uH | holo:SRR6038 | SRR6038-180YCT-ND | 1 | 2 | Bourns | SRR6038-180Y | https://www.digikey.at/products/de?keywords=SRR6038-180YCT-ND | 0.72 | 1.44
> LS601, LS701, LS801, LS901, LS1001, LS1101, LS1201, LS1301, LS1401, LS1501, L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 | Speaker_Ultrasound | holo:MSO-P1040H07T |  | 100 | 200 | Manorshi | MSO-P1040H07T |  | 0.56999999999999995 | 113.99999999999999 | !!!ALIBABA 286 USD = 236€ for 410pcs!!!
PS301 | OKI-T36W-W40 | holo:OKI-T-36W-W40 | 811-3132-1-ND | 1 | 2 | Murata | OKI-T/36W-W40P-C | https://www.digikey.at/products/de?keywords=811-3132-1-ND | 9.1 | 18.2
R101 | 330R | Resistor_SMD:R_0402_1005Metric | 541-3996-1-ND | 1 | 2 |  |  | MTE-Sample Resistors ELAB |  | 0
R103 | 1.0K | Resistor_SMD:R_0402_1005Metric | A127319CT-ND | 1 | 2 |  |  | MTE-Sample Resistors ELAB |  | 0
> R102, R104, R201-R207, R11001-R11007 | 10K | Resistor_SMD:R_0402_1005Metric | RMCF0402JT10K0CT | 16 | 32 |  |  | MTE-Sample Resistors ELAB |  | 0
R105 | 0R | Resistor_SMD:R_0402_1005Metric | ~ | 1 | 2 |  |  | MTE-Sample Resistors ELAB |  | 0
R106 | 0R | Jumper:SolderJumper-2_P1.3mm_Open_TrianglePad1.0x1.5mm | ~ | 1 | 2 |  |  | MTE-Sample Resistors ELAB |  | 0
> R107-R110 | 100R | Resistor_SMD:R_0402_1005Metric | A127223CT-ND | 4 | 8 |  |  | MTE-Sample Resistors ELAB |  | 0
> R208, R11008 | 24R9 | Resistor_SMD:R_0402_1005Metric | 2037-PFR05S-24R9-FNHCT-ND | 2 | 4 | Delta | PFR05S-24R9-FNH | https://www.digikey.at/products/de?keywords=2037-PFR05S-24R9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 | 0.09 | 0.36
R301 | 52R21 | Resistor_SMD:R_0603_1608Metric | RMCF0603FT26R1CT-ND | 1 | 2 | Stackpole | RMCF0603FT26R1 | https://www.digikey.at/products/de?keywords=RMCF0603FT26R1CT-ND | 0.09 | 0.18
> R302, R303, R309 | 100K | Resistor_SMD:R_0402_1005Metric | RMCS0402JT100KCT-ND | 3 | 6 |  |  | MTE-Sample Resistors ELAB |  | 0
R304 | 47K | Resistor_SMD:R_0402_1005Metric | 541-3966-1-ND | 1 | 2 |  |  | MTE-Sample Resistors ELAB |  | 0
R305 | 5.0K | Resistor_SMD:R_0402_1005Metric | 541-3972-1-ND | 1 | 2 | Vishay | CRCW04024K99FKEDC | https://www.digikey.at/products/de?keywords=541-3972-1-ND | 0.09 | 0.18
R306 | 10.31K | Resistor_SMD:R_0402_1005Metric | RR12P10.2KDCT-ND | 1 | 2 | Susumu | RR1220P-1022-D-M | https://www.digikey.at/products/de?keywords=RR12P10.2KDCT-ND | 0.09 | 0.18
> R307, R310 | 75K | Resistor_SMD:R_0402_1005Metric | 541-5078-1-ND | 2 | 4 |  |  | MTE-Sample Resistors ELAB |  | 0
R308 | 27.6K | Resistor_SMD:R_0402_1005Metric | CR0402-FX-27R4GLFCT-ND | 1 | 2 | Bourns | CR0402-FX-27R4GLF | https://www.digikey.at/products/de?keywords=CR0402-FX-27R4GLFCT-ND | 0.09 | 0.18
R311 | 14.46K | Resistor_SMD:R_0402_1005Metric | YAG2983CT-ND | 1 | 2 | Yageo | RC0402FR-0714K3L | https://www.digikey.at/products/de?keywords=YAG2983CT-ND | 0.09 | 0.18
> R10701, R10801, R10901 | 40K | Resistor_SMD:R_0402_1005Metric | CR0402-FX-4022GLFCT-ND | 3 | 6 | Bourns | CR0402-FX-4022GLF | https://www.digikey.at/products/de?keywords=CR0402-FX-4022GLFCT-ND | 0.09 | 0.54
> R10702, R10802, R10902 | 8.9K | Resistor_SMD:R_0402_1005Metric | RMCF0402FT8K87CT-ND | 3 | 6 | Stackpole | RMCF0402FT8K87 | https://www.digikey.at/products/de?keywords=RMCF0402FT8K87CT-ND | 0.09 | 0.54
SBC401 | Raspberry_Pi_2_3 | Module:Raspberry_Pi_Zero_Socketed_THT_MountingHoles_SMT |  | 0 | 0 |  | RASP PI ZERO W | https://www.reichelt.at/at/de/raspberry-pi-zero-w-v-1-1-1-gh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 | 19.77 | 0
SW101 | SW_Push | Button_Switch_SMD:SW_SPST_KMR2 | CKN10246CT-ND | 0 | 0 |  |  |  |  | 0
U101 | AM26LV32CDR | Package_SO:SOIC-16_3.9x9.9mm_P1.27mm | 296-6794-1-ND | 1 | 2 | TI | AM26LV32CDR | https://www.digikey.at/products/de?keywords=296-6794-1-ND | 0.8 | 1.6
U102 | AM26LV31 | Package_SO:SOIC-16_3.9x9.9mm_P1.27mm | 296-25912-1-ND | 1 | 2 | TI | AM26LV31CDR | https://www.digikey.at/products/de?keywords=296-25912-1-ND | 0.87 | 1.74
> U201, U11001 | 10CL010YE144C8G | Package_QFP:EQFP-144-1EP_20x20mm_P0.5mm_EP6.7x6.7mm | 544-3578-ND | 2 | 4 | Intel / Altera | 10CL010YE144C8G | https://www.digikey.at/products/de?keywords=10CL010YE144C8G | 8.08 | 32.32 | alternate: 10CL010YE144I7G, ggf arrow samples?
> U202, U11002 | MIC5504-2.5YM5 | Package_TO_SOT_SMD:SOT-23-5 | 576-4880-1-ND | 2 | 4 | Microchip | MIC5504-2.5YM5-TR | https://www.digikey.at/products/de?keywords=576-4880-1-ND | 0.11 | 0.44
> U203, U11003 | EPCQ16A | Package_SO:SOIC-8_3.9x4.9mm_P1.27mm | 544-3440-ND | 2 | 4 | Intel | EPCQ16ASI8N | https://www.digikey.at/products/de?keywords=EPCQ16ASI8N | 5.79 | 23.16
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
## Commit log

2021-03-27 edited schematic according to board errata
    added missing connections, jumpers and PDs
2021-03-27 fixed wiring, removed unecessary 2V5 connection
2021-04-06 PCB 1V1
    see changelog.txt
2021-04-10 silk screen error fixed
2021-04-18 added mounting holes
2021-05-17 Create vdatp_bom_MTE.xlsx
    BOM mit Bestell-Links und Berücksichtigung der MTE Lagrestände
2021-06-01 generated gerbers
2023-10-12 KICAD 7.0
    -converted PCB project to KICAD 7.0
    -generated PCBA assembly documents (pdf)
2023-10-27 pictures of PCBA
    *added 2 pics from Dan
    *added pcb outline for lasercut
2023-12-21 documentation updated
    pick & place
